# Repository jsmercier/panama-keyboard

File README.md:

# panama-keyboard
Custom keyboard project using ATmega32A

Only left missing is the hex file for the QMK firmware, will add soon.

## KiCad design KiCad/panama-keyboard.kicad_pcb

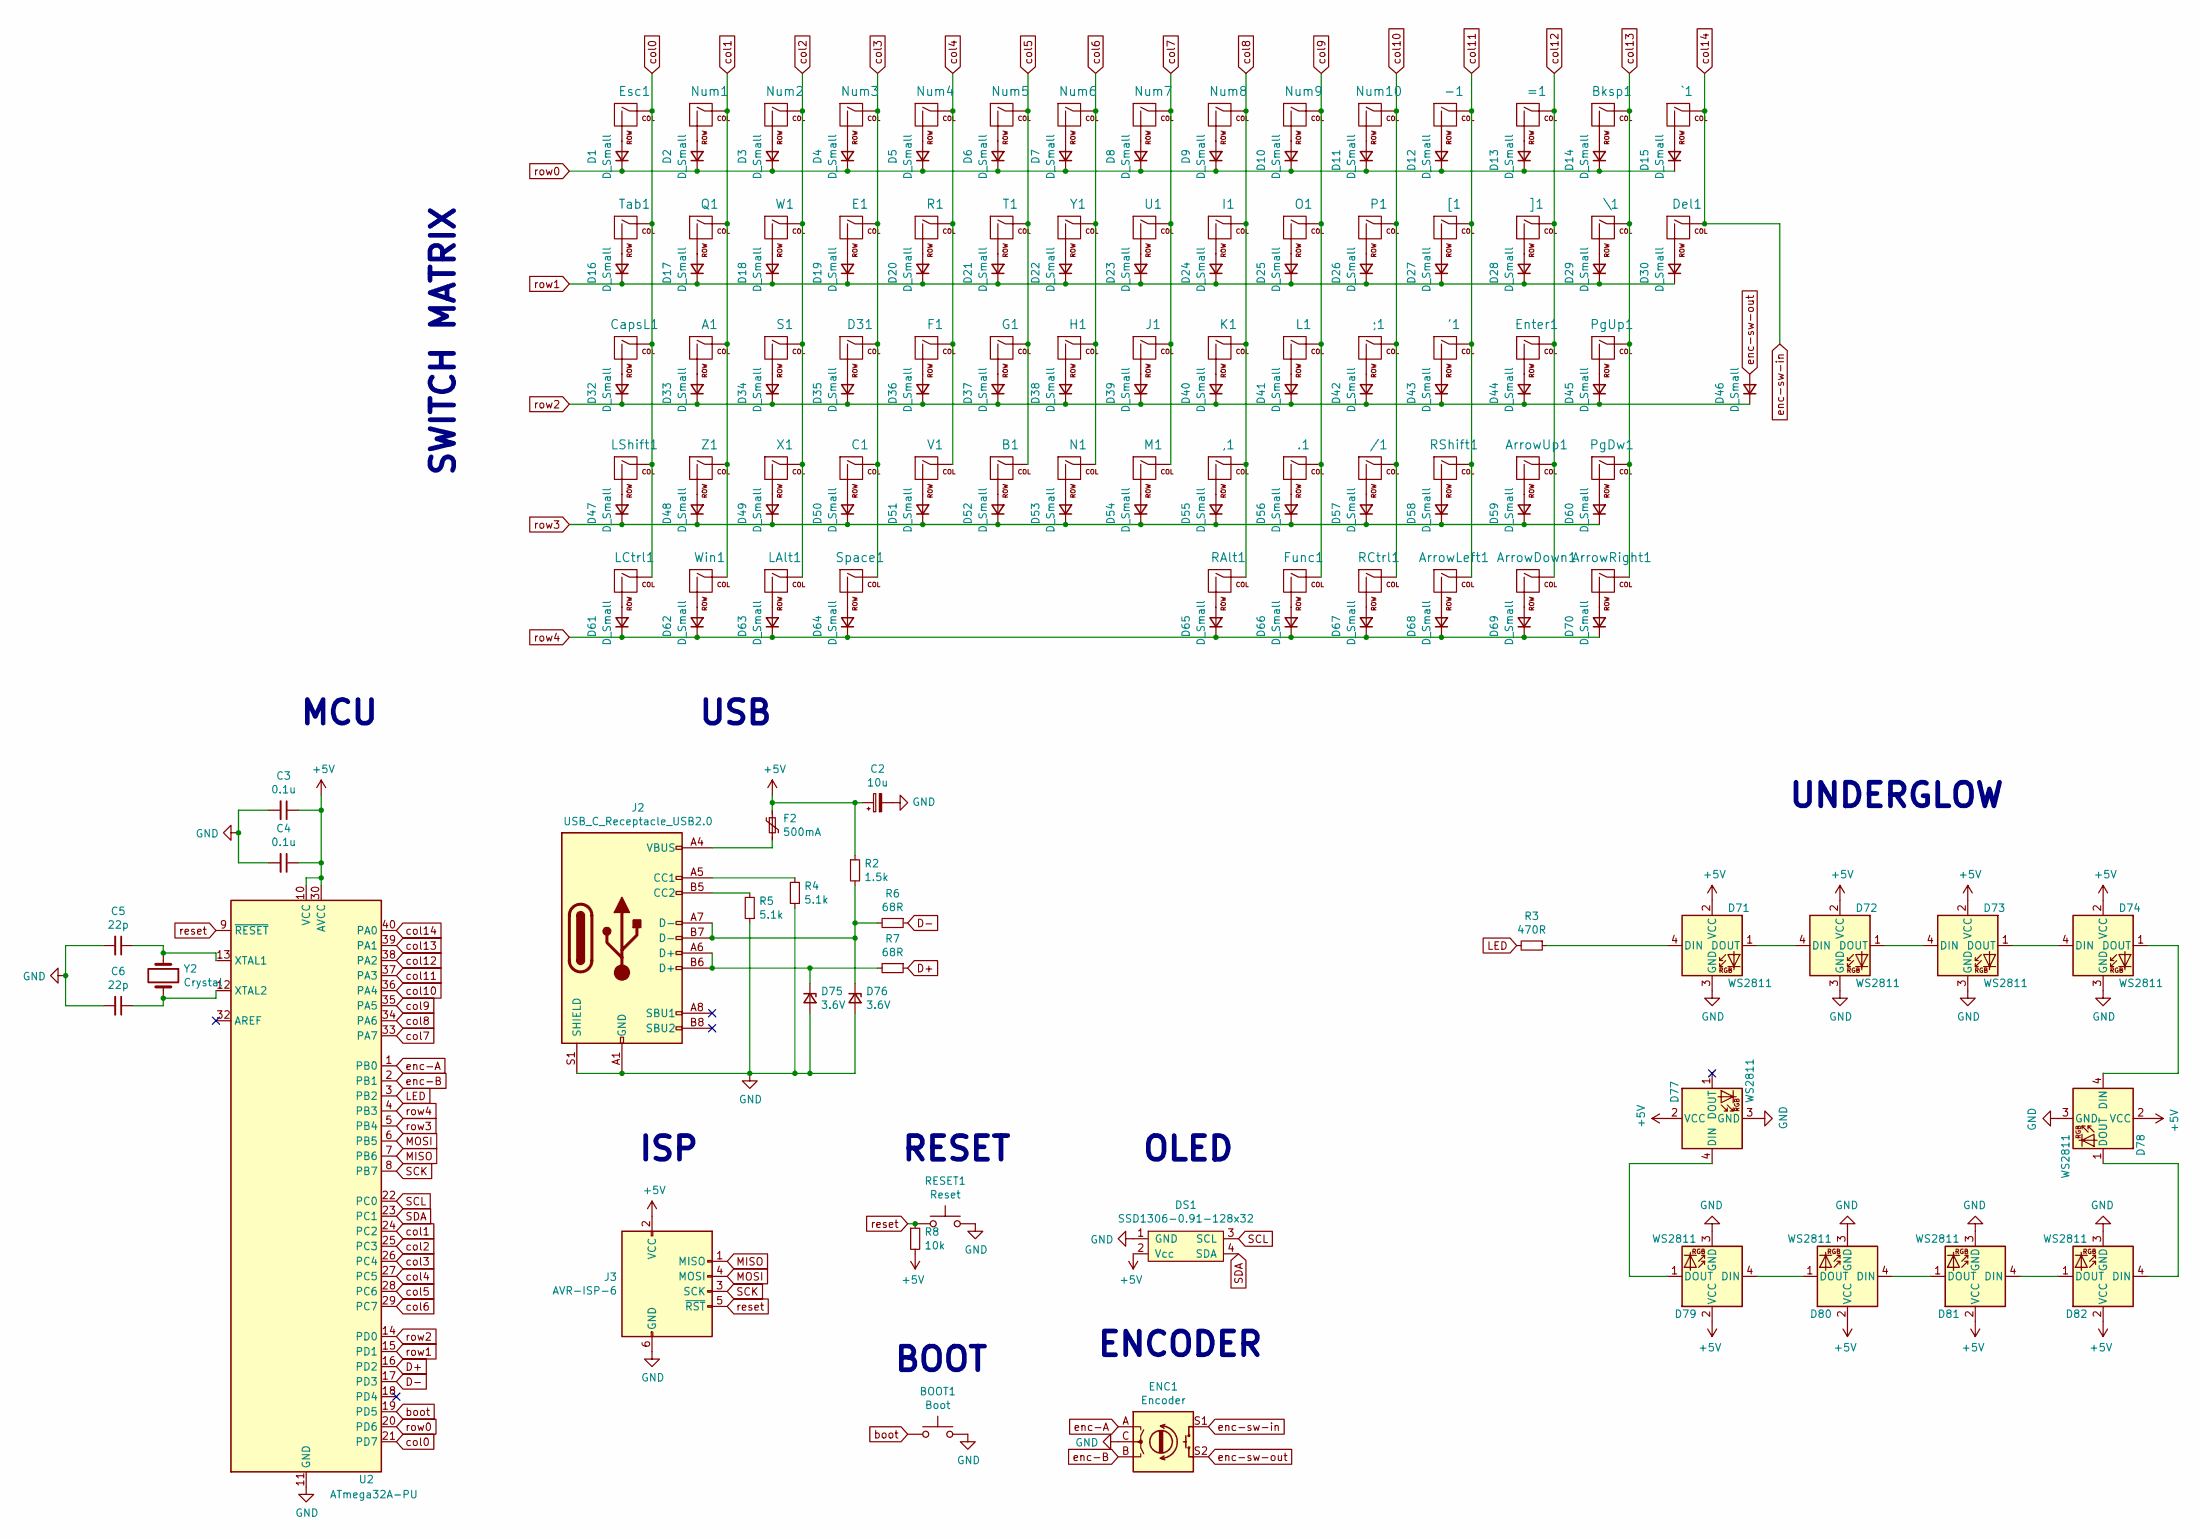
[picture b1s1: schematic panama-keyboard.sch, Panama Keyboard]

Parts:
'1: MX; SW_Cherry_MX_1.00u_PCB
,1: MX; SW_Cherry_MX_1.00u_PCB
-1: MX; SW_Cherry_MX_1.00u_PCB
.1: MX; SW_Cherry_MX_1.00u_PCB
/1: MX; SW_Cherry_MX_1.00u_PCB
;1: MX; SW_Cherry_MX_1.00u_PCB
=1: MX; SW_Cherry_MX_1.00u_PCB
A1: MX; SW_Cherry_MX_1.00u_PCB
ArrowDown1: MX; SW_Cherry_MX_1.00u_PCB
ArrowLeft1: MX; SW_Cherry_MX_1.00u_PCB
ArrowRight1: MX; SW_Cherry_MX_1.00u_PCB
ArrowUp1: MX; SW_Cherry_MX_1.00u_PCB
B1: MX; SW_Cherry_MX_1.00u_PCB
BOOT1: Boot; SW_PUSH_6mm
Bksp1: MX; SW_Cherry_MX_2.00u_PCB
C1: MX; SW_Cherry_MX_1.00u_PCB
C2: 10u; CP_Radial_D5.0mm_P2.00mm
C3, C4: 0.1u; C_Disc_D5.0mm_W2.5mm_P5.00mm
C5, C6: 22p; C_Disc_D5.0mm_W2.5mm_P5.00mm
CapsL1: MX; SW_Cherry_MX_1.75u_PCB
D1, D2, D3, D4, D5, D6, D7, D8, D9, D10, D11, D12, D13, D14, D15, D16, D17, D18, D19, D20, D21, D22, D23, D24, D25, D26, D27, D28, D29, D30, D32, D33, D34, D35, D36, D37, D38, D39, D40, D41, D42, D43, D44, D45, D46, D47, D48, D49, D50, D51, D52, D53, D54, D55, D56, D57, D58, D59, D60, D61, D62, D63, D64, D65, D66, D67, D68, D69, D70: D_Small; D_DO-35_SOD27_P7.62mm_Horizontal
D31: MX; SW_Cherry_MX_1.00u_PCB
D71, D72, D73, D74, D77, D78, D79, D80, D81, D82: WS2811; LED_D5.0mm-4_RGB
D75, D76: 3.6V; D_DO-35_SOD27_P7.62mm_Horizontal
DS1: SSD1306-0.91-128x32; OLED_0.91in_128x32
Del1: MX; SW_Cherry_MX_1.00u_PCB
E1: MX; SW_Cherry_MX_1.00u_PCB
ENC1: Encoder; RotaryEncoder_Alps_EC11E-Switch_Vertical_H20mm
Enter1: MX; SW_Cherry_MX_2.25u_PCB
Esc1: MX; SW_Cherry_MX_1.00u_PCB
F1: MX; SW_Cherry_MX_1.00u_PCB
F2: 500mA; Fuse_BelFuse_0ZRE0005FF_L8.3mm_W3.8mm
Func1: MX; SW_Cherry_MX_1.00u_PCB
G1: MX; SW_Cherry_MX_1.00u_PCB
H1: MX; SW_Cherry_MX_1.00u_PCB
I1: MX; SW_Cherry_MX_1.00u_PCB
J1: MX; SW_Cherry_MX_1.00u_PCB
J2: USB_C_Receptacle_USB2.0; USB_C_Receptacle_GCT_USB4085
J3: AVR-ISP-6; PinHeader_1x06_P2.54mm_Horizontal
K1: MX; SW_Cherry_MX_1.00u_PCB
L1: MX; SW_Cherry_MX_1.00u_PCB
LAlt1: MX; SW_Cherry_MX_1.25u_PCB
LCtrl1: MX; SW_Cherry_MX_1.25u_PCB
LShift1: MX; SW_Cherry_MX_2.25u_PCB
M1: MX; SW_Cherry_MX_1.00u_PCB
N1: MX; SW_Cherry_MX_1.00u_PCB
Num1, Num2, Num3, Num4, Num5, Num6, Num7, Num8, Num9, Num10: MX; SW_Cherry_MX_1.00u_PCB
O1: MX; SW_Cherry_MX_1.00u_PCB
P1: MX; SW_Cherry_MX_1.00u_PCB
PgDw1: MX; SW_Cherry_MX_1.00u_PCB
PgUp1: MX; SW_Cherry_MX_1.00u_PCB
Q1: MX; SW_Cherry_MX_1.00u_PCB
R1: MX; SW_Cherry_MX_1.00u_PCB
R2: 1.5k; R_Axial_DIN0204_L3.6mm_D1.6mm_P5.08mm_Horizontal
R3: 470R; R_Axial_DIN0204_L3.6mm_D1.6mm_P5.08mm_Horizontal
R4, R5: 5.1k; R_Axial_DIN0204_L3.6mm_D1.6mm_P5.08mm_Horizontal
R6, R7: 68R; R_Axial_DIN0204_L3.6mm_D1.6mm_P5.08mm_Horizontal
R8: 10k; R_Axial_DIN0204_L3.6mm_D1.6mm_P5.08mm_Horizontal
RAlt1: MX; SW_Cherry_MX_1.00u_PCB
RCtrl1: MX; SW_Cherry_MX_1.00u_PCB
RESET1: Reset; SW_PUSH_6mm
RShift1: MX; SW_Cherry_MX_1.75u_PCB
S1: MX; SW_Cherry_MX_1.00u_PCB
Space1: MX; SW_Cherry_MX_6.25u_PCB
T1: MX; SW_Cherry_MX_1.00u_PCB
Tab1: MX; SW_Cherry_MX_1.50u_PCB
U1: MX; SW_Cherry_MX_1.00u_PCB
U2: ATmega32A-PU; DIP-40_W15.24mm_Socket
V1: MX; SW_Cherry_MX_1.00u_PCB
W1: MX; SW_Cherry_MX_1.00u_PCB
Win1: MX; SW_Cherry_MX_1.25u_PCB
X1: MX; SW_Cherry_MX_1.00u_PCB
Y1: MX; SW_Cherry_MX_1.00u_PCB
Y2: Crystal; Crystal_HC49-U_Vertical
Z1: MX; SW_Cherry_MX_1.00u_PCB
[1: MX; SW_Cherry_MX_1.00u_PCB
\1: MX; SW_Cherry_MX_1.50u_PCB
]1: MX; SW_Cherry_MX_1.00u_PCB
`1: MX; SW_Cherry_MX_1.00u_PCB

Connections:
+5V: C2.1, C3.1, C4.1, D71.2 (VCC), D72.2 (VCC), D73.2 (VCC), D74.2 (VCC), D77.2 (VCC), D78.2 (VCC), D79.2 (VCC), D80.2 (VCC), D81.2 (VCC), D82.2 (VCC), DS1.2 (Vcc), F2.1, J3.2 (VCC), R2.1, R8.2, U2.10 (VCC), U2.30 (AVCC)
D+: R7.1, U2.16 (PD2)
D-: R6.1, U2.17 (PD3)
GND: BOOT1.2, C2.2, C3.2, C4.2, C5.2, C6.2, D71.3 (GND), D72.3 (GND), D73.3 (GND), D74.3 (GND), D75.2 (A), D76.2 (A), D77.3 (GND), D78.3 (GND), D79.3 (GND), D80.3 (GND), D81.3 (GND), D82.3 (GND), DS1.1 (GND), ENC1.C, J2.A1 (GND), J2.A12 (GND), J2.B1 (GND), J2.B12 (GND), J2.S1 (SHIELD), J3.6 (GND), R4.1, R5.1, RESET1.2, U2.11 (GND), U2.31 (GND)
LED: R3.2, U2.3 (PB2)
MISO: J3.1 (MISO), U2.7 (PB6)
MOSI: J3.4 (MOSI), U2.6 (PB5)
unnamed: '1.2 (ROW), D43.2 (A)
unnamed: ,1.2 (ROW), D55.2 (A)
unnamed: -1.2 (ROW), D12.2 (A)
unnamed: .1.2 (ROW), D56.2 (A)
unnamed: /1.2 (ROW), D57.2 (A)
unnamed: ;1.2 (ROW), D42.2 (A)
unnamed: =1.2 (ROW), D13.2 (A)
unnamed: A1.2 (ROW), D33.2 (A)
unnamed: ArrowDown1.2 (ROW), D69.2 (A)
unnamed: ArrowLeft1.2 (ROW), D68.2 (A)
unnamed: ArrowRight1.2 (ROW), D70.2 (A)
unnamed: ArrowUp1.2 (ROW), D59.2 (A)
unnamed: B1.2 (ROW), D52.2 (A)
unnamed: Bksp1.2 (ROW), D14.2 (A)
unnamed: C1.2 (ROW), D50.2 (A)
unnamed: C5.1, U2.13 (XTAL1), Y2.1
unnamed: C6.1, U2.12 (XTAL2), Y2.2
unnamed: CapsL1.2 (ROW), D32.2 (A)
unnamed: D1.2 (A), Esc1.2 (ROW)
unnamed: D2.2 (A), Num1.2 (ROW)
unnamed: D3.2 (A), Num2.2 (ROW)
unnamed: D4.2 (A), Num3.2 (ROW)
unnamed: D5.2 (A), Num4.2 (ROW)
unnamed: D6.2 (A), Num5.2 (ROW)
unnamed: D7.2 (A), Num6.2 (ROW)
unnamed: D8.2 (A), Num7.2 (ROW)
unnamed: D9.2 (A), Num8.2 (ROW)
unnamed: D10.2 (A), Num9.2 (ROW)
unnamed: D11.2 (A), Num10.2 (ROW)
unnamed: D15.2 (A), `1.2 (ROW)
unnamed: D16.2 (A), Tab1.2 (ROW)
unnamed: D17.2 (A), Q1.2 (ROW)
unnamed: D18.2 (A), W1.2 (ROW)
unnamed: D19.2 (A), E1.2 (ROW)
unnamed: D20.2 (A), R1.2 (ROW)
unnamed: D21.2 (A), T1.2 (ROW)
unnamed: D22.2 (A), Y1.2 (ROW)
unnamed: D23.2 (A), U1.2 (ROW)
unnamed: D24.2 (A), I1.2 (ROW)
unnamed: D25.2 (A), O1.2 (ROW)
unnamed: D26.2 (A), P1.2 (ROW)
unnamed: D27.2 (A), [1.2 (ROW)
unnamed: D28.2 (A), ]1.2 (ROW)
unnamed: D29.2 (A), \1.2 (ROW)
unnamed: D30.2 (A), Del1.2 (ROW)
unnamed: D31.2 (ROW), D35.2 (A)
unnamed: D34.2 (A), S1.2 (ROW)
unnamed: D36.2 (A), F1.2 (ROW)
unnamed: D37.2 (A), G1.2 (ROW)
unnamed: D38.2 (A), H1.2 (ROW)
unnamed: D39.2 (A), J1.2 (ROW)
unnamed: D40.2 (A), K1.2 (ROW)
unnamed: D41.2 (A), L1.2 (ROW)
unnamed: D44.2 (A), Enter1.2 (ROW)
unnamed: D45.2 (A), PgUp1.2 (ROW)
unnamed: D47.2 (A), LShift1.2 (ROW)
unnamed: D48.2 (A), Z1.2 (ROW)
unnamed: D49.2 (A), X1.2 (ROW)
unnamed: D51.2 (A), V1.2 (ROW)
unnamed: D53.2 (A), N1.2 (ROW)
unnamed: D54.2 (A), M1.2 (ROW)
unnamed: D58.2 (A), RShift1.2 (ROW)
unnamed: D60.2 (A), PgDw1.2 (ROW)
unnamed: D61.2 (A), LCtrl1.2 (ROW)
unnamed: D62.2 (A), Win1.2 (ROW)
unnamed: D63.2 (A), LAlt1.2 (ROW)
unnamed: D64.2 (A), Space1.2 (ROW)
unnamed: D65.2 (A), RAlt1.2 (ROW)
unnamed: D66.2 (A), Func1.2 (ROW)
unnamed: D67.2 (A), RCtrl1.2 (ROW)
unnamed: D71.1 (DOUT), D72.4 (DIN)
unnamed: D71.4 (DIN), R3.1
unnamed: D72.1 (DOUT), D73.4 (DIN)
unnamed: D73.1 (DOUT), D74.4 (DIN)
unnamed: D74.1 (DOUT), D78.4 (DIN)
unnamed: D75.1 (K), J2.A6 (D+), J2.B6 (D+), R7.2
unnamed: D76.1 (K), J2.A7 (D-), J2.B7 (D-), R2.2, R6.2
unnamed: D77.4 (DIN), D79.1 (DOUT)
unnamed: D78.1 (DOUT), D82.4 (DIN)
unnamed: D79.4 (DIN), D80.1 (DOUT)
unnamed: D80.4 (DIN), D81.1 (DOUT)
unnamed: D81.4 (DIN), D82.1 (DOUT)
unnamed: F2.2, J2.A4 (VBUS), J2.A9 (VBUS), J2.B4 (VBUS), J2.B9 (VBUS)
unnamed: J2.A5 (CC1), R4.2
unnamed: J2.B5 (CC2), R5.2
SCK: J3.3 (SCK), U2.8 (PB7)
SCL: DS1.3 (SCL), U2.22 (PC0)
SDA: DS1.4 (SDA), U2.23 (PC1)
boot: BOOT1.1, U2.19 (PD5)
col0: CapsL1.1 (COL), Esc1.1 (COL), LCtrl1.1 (COL), LShift1.1 (COL), Tab1.1 (COL), U2.21 (PD7)
col1: A1.1 (COL), Num1.1 (COL), Q1.1 (COL), U2.24 (PC2), Win1.1 (COL), Z1.1 (COL)
col2: LAlt1.1 (COL), Num2.1 (COL), S1.1 (COL), U2.25 (PC3), W1.1 (COL), X1.1 (COL)
col3: C1.1 (COL), D31.1 (COL), E1.1 (COL), Num3.1 (COL), Space1.1 (COL), U2.26 (PC4)
col4: F1.1 (COL), Num4.1 (COL), R1.1 (COL), U2.27 (PC5), V1.1 (COL)
col5: B1.1 (COL), G1.1 (COL), Num5.1 (COL), T1.1 (COL), U2.28 (PC6)
col6: H1.1 (COL), N1.1 (COL), Num6.1 (COL), U2.29 (PC7), Y1.1 (COL)
col7: J1.1 (COL), M1.1 (COL), Num7.1 (COL), U1.1 (COL), U2.33 (PA7)
col8: ,1.1 (COL), I1.1 (COL), K1.1 (COL), Num8.1 (COL), RAlt1.1 (COL), U2.34 (PA6)
col9: .1.1 (COL), Func1.1 (COL), L1.1 (COL), Num9.1 (COL), O1.1 (COL), U2.35 (PA5)
col10: /1.1 (COL), ;1.1 (COL), Num10.1 (COL), P1.1 (COL), RCtrl1.1 (COL), U2.36 (PA4)
col11: '1.1 (COL), -1.1 (COL), ArrowLeft1.1 (COL), RShift1.1 (COL), U2.37 (PA3), [1.1 (COL)
col12: =1.1 (COL), ArrowDown1.1 (COL), ArrowUp1.1 (COL), Enter1.1 (COL), U2.38 (PA2), ]1.1 (COL)
col13: ArrowRight1.1 (COL), Bksp1.1 (COL), PgDw1.1 (COL), PgUp1.1 (COL), U2.39 (PA1), \1.1 (COL)
col14: Del1.1 (COL), ENC1.S1, U2.40 (PA0), `1.1 (COL)
enc-A: ENC1.A, U2.1 (PB0)
enc-B: ENC1.B, U2.2 (PB1)
enc-sw-out: D46.2 (A), ENC1.S2
reset: J3.5 (~RST), R8.1, RESET1.1, U2.9 (~RESET)
row0: D1.1 (K), D2.1 (K), D3.1 (K), D4.1 (K), D5.1 (K), D6.1 (K), D7.1 (K), D8.1 (K), D9.1 (K), D10.1 (K), D11.1 (K), D12.1 (K), D13.1 (K), D14.1 (K), D15.1 (K), U2.20 (PD6)
row1: D16.1 (K), D17.1 (K), D18.1 (K), D19.1 (K), D20.1 (K), D21.1 (K), D22.1 (K), D23.1 (K), D24.1 (K), D25.1 (K), D26.1 (K), D27.1 (K), D28.1 (K), D29.1 (K), D30.1 (K), U2.15 (PD1)
row2: D32.1 (K), D33.1 (K), D34.1 (K), D35.1 (K), D36.1 (K), D37.1 (K), D38.1 (K), D39.1 (K), D40.1 (K), D41.1 (K), D42.1 (K), D43.1 (K), D44.1 (K), D45.1 (K), D46.1 (K), U2.14 (PD0)
row3: D47.1 (K), D48.1 (K), D49.1 (K), D50.1 (K), D51.1 (K), D52.1 (K), D53.1 (K), D54.1 (K), D55.1 (K), D56.1 (K), D57.1 (K), D58.1 (K), D59.1 (K), D60.1 (K), U2.5 (PB4)
row4: D61.1 (K), D62.1 (K), D63.1 (K), D64.1 (K), D65.1 (K), D66.1 (K), D67.1 (K), D68.1 (K), D69.1 (K), D70.1 (K), U2.4 (PB3)

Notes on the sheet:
SWITCH MATRIX
UNDERGLOW
BOOT
RESET
OLED
ENCODER
ISP
USB
MCU

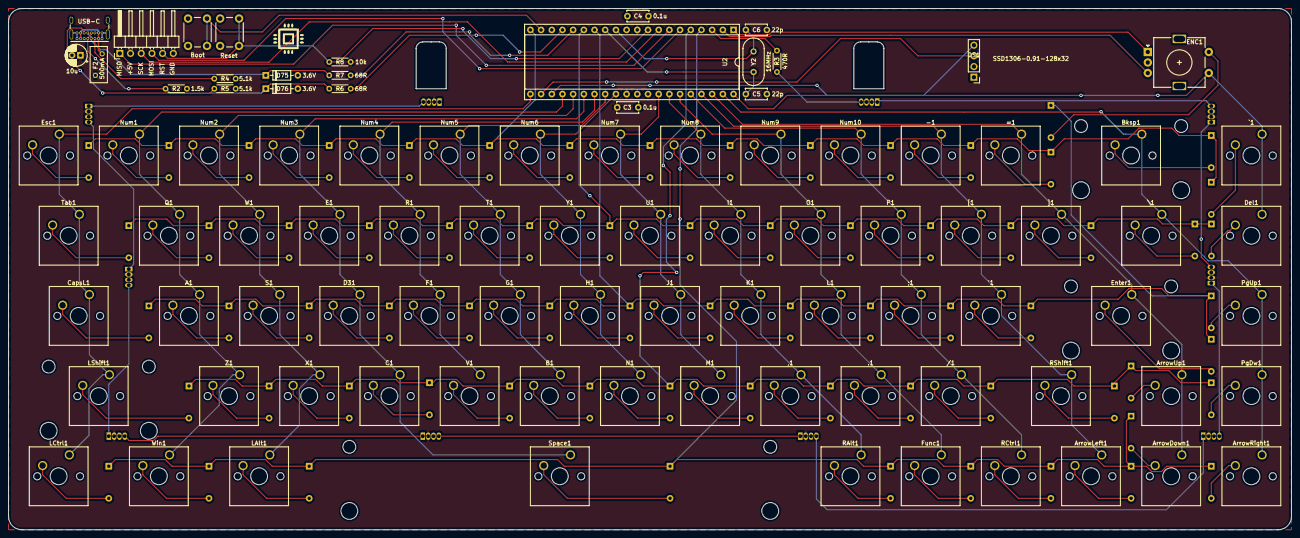
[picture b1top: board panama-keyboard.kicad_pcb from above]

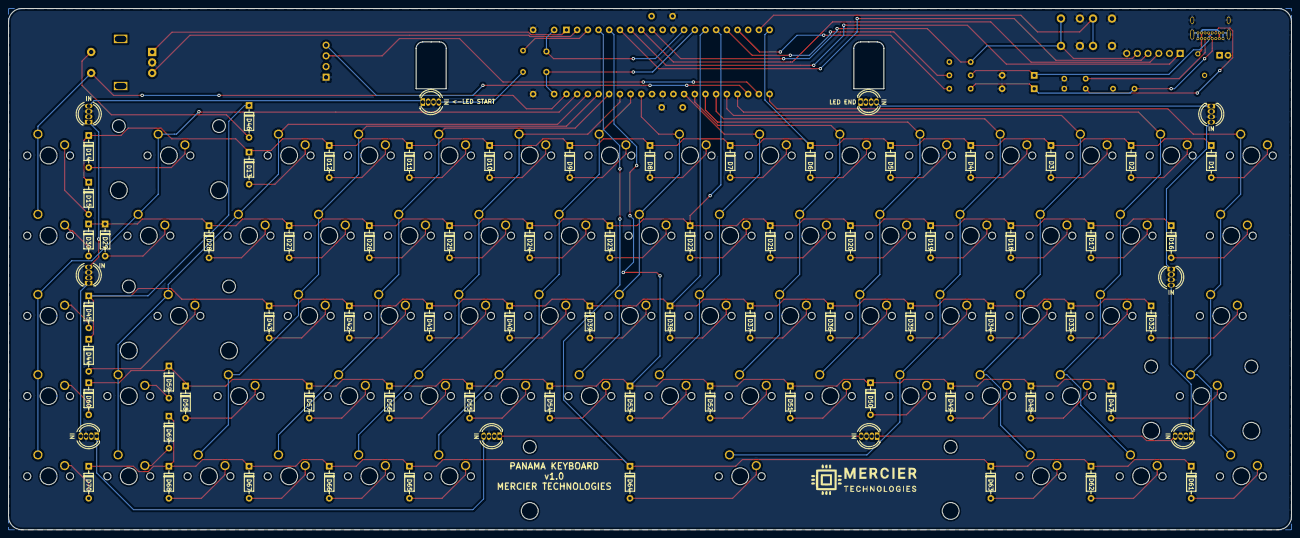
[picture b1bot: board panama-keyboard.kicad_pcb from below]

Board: 2 copper layers, 304.8 x 123.8 mm, 170 parts (79 on the bottom side), 120 nets.

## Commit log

2020-07-15 working issue
2020-07-15 removed useless sub folder
2020-07-15 added lib
2020-07-16 added switch matrix and mcu
2020-07-19 schematic progress
2020-07-20 footprint added except MX
2020-07-22 finished w1 schematic, started PCB
2020-07-23 progree pcb
2020-07-24 pcb progress
2020-07-27 pcb progress, back to 10 leds
2020-07-31 pcb progress, moved switch matrix
2020-07-31 logo added, PCB done
2020-07-31 added usb c connector model
2020-07-31 added gerber files
2020-08-01 added 3d models
2020-08-02 pinout changed, pcb trace to be reworked
2020-08-03 traces removed for new pinout
2020-08-03 pcb rework done
2020-08-03 pcb height adjust
2020-08-04 organized Creo folder
2020-08-05 3d progress
2020-08-07 silkscreen pcb update
2020-08-07 removed Creo folder
2020-08-08 added DXF and BoM
2020-08-08 updated gerber
2020-08-12 test remote
2021-01-03 QMK folder
2021-01-03 QMK firmware files added
2021-01-03 USBasp files added for flashing the atmega32A
